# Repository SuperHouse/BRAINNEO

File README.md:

Building Brain Home Automation Controller (NanoPi NEO version)
===============================================================
Copyright 2017 SuperHouse Automation Pty Ltd  www.superhouse.tv  

Home automation controller based on a NanoPi NEO. The NEO
attaches to this board, which is Arduino-compatible (ATmega328P) and
includes 433MHz transmitter and receiver modules connected to the
Arduino. The Arduino can communicate with the NEO via serial, and
can send / receive RF messages using the 433MHz modules.

Features:

 * ATmega328P MCU
 * 433MHz transmitter
 * 433MHz receiver
 * Status LEDs

INSTALLATION
------------
The design is saved as an EAGLE project. EAGLE PCB design software is
available from www.cadsoftusa.com free for non-commercial use. To use
this project download it and place the directory containing these files
into the "eagle" directory on your computer. Then open EAGLE and
navigate to the project.

CREDITS
-------
Designed by Jonathan Oxer jon@oxer.com.au

DISTRIBUTION
------------
The specific terms of distribution of this project are governed by the
license referenced below.

LICENSE
-------
Licensed under the TAPR Open Hardware License (www.tapr.org/OHL).
The "license" folder within this repository also contains a copy of
this license in plain text format.

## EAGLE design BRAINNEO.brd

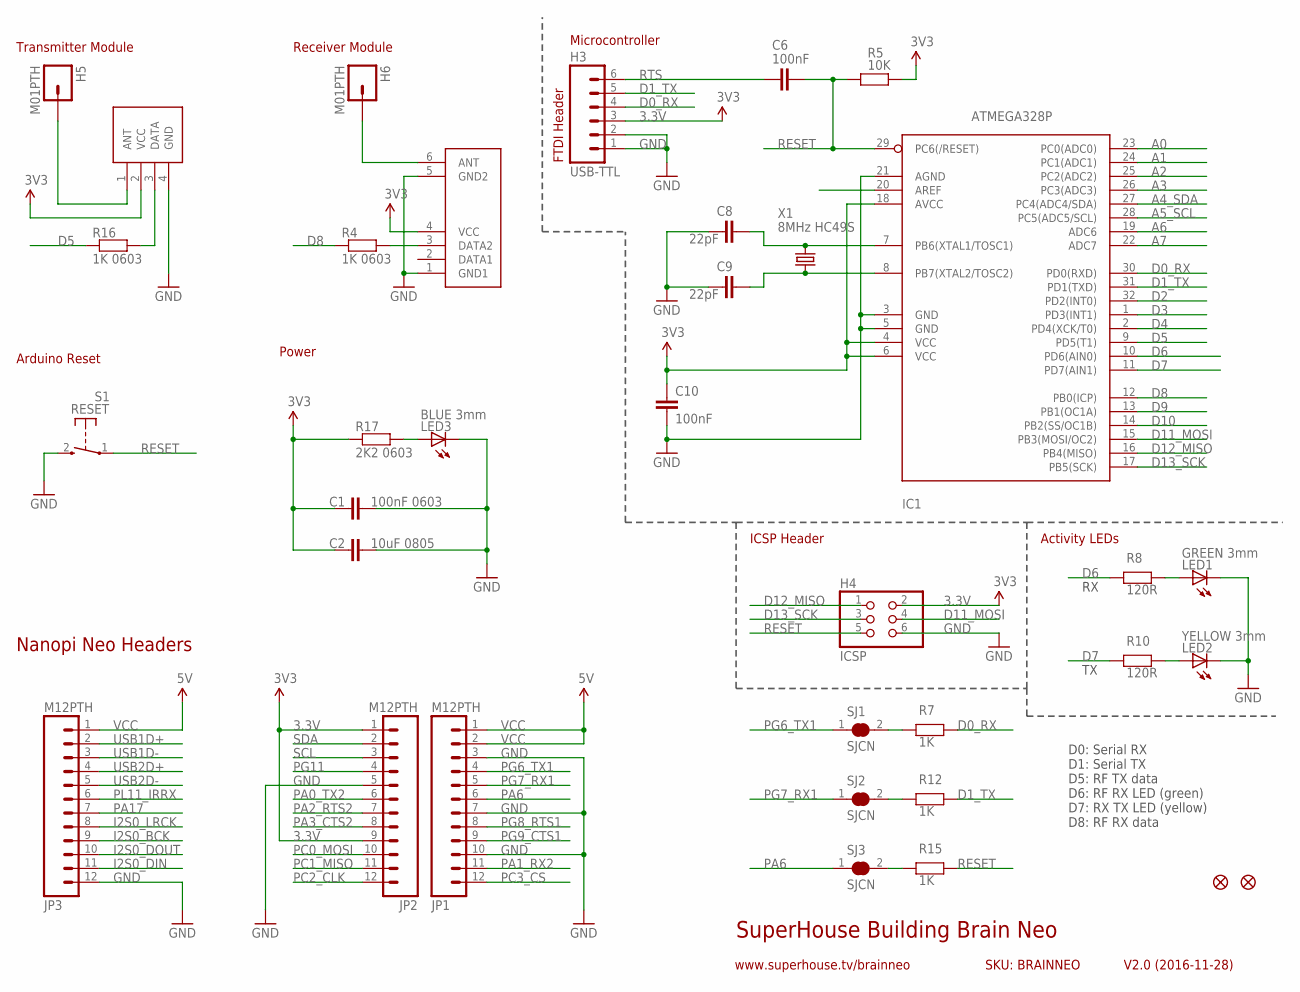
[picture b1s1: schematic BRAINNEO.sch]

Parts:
C1: 100nF 0603; 0603
C2: 10uF 0805; C0805
C6, C10: 100nF; 0603
C8, C9: 22pF; 0603
H3: USB-TTL; 1X06
H4: ICSP; 2X03
H5, H6: M01PTH; 1X01
IC1: ATMEGA328P; TQFP32-08
IC3: RXB1; RX-B1-SHORT-FLAT
IC4: TX-C1FLAT; TX-C1-FLAT
JP1, JP2, JP3: M12PTH; 1X12
LED1: GREEN 3mm; LED3MM
LED2: YELLOW 3mm; LED3MM
LED3: BLUE 3mm; LED3MM
R4, R16: 1K 0603; 0603
R5: 10K; 0603
R7, R12, R15: 1K; 0603
R8, R10: 120R; 0603
R17: 2K2 0603; 0603
S1: RESET; TACTILE_SWITCH_SMD_2PIN_TINY
SJ1, SJ2, SJ3: SJCN; SJC
U$5, U$6: FIDUCIAL1X2.5; FIDUCIAL-1X2.5
X1: 8MHz HC49S; HC49U-V

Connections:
3.3V: C1.1, C2.2, C10.1, H3.3, H4.2, IC1.4 (VCC), IC1.6 (VCC), IC1.18 (AVCC), IC3.4 (VCC), IC4.2 (VCC), JP2.1, JP2.9, R5.2, R17.1
A0: IC1.23 (PC0(ADC0))
A1: IC1.24 (PC1(ADC1))
A2: IC1.25 (PC2(ADC2))
A3: IC1.26 (PC3(ADC3))
A4_SDA: IC1.27 (PC4(ADC4/SDA))
A5_SCL: IC1.28 (PC5(ADC5/SCL))
A6: IC1.19 (ADC6)
A7: IC1.22 (ADC7)
AREF: IC1.20 (AREF)
D0_RX: H3.4, IC1.30 (PD0(RXD)), R7.1
D1_TX: H3.5, IC1.31 (PD1(TXD)), R12.1
D2: IC1.32 (PD2(INT0))
D3: IC1.1 (PD3(INT1))
D4: IC1.2 (PD4(XCK/T0))
D5: IC1.9 (PD5(T1)), R16.1
D6: IC1.10 (PD6(AIN0)), R8.2
D7: IC1.11 (PD7(AIN1)), R10.2
D8: IC1.12 (PB0(ICP)), R4.1
D9: IC1.13 (PB1(OC1A))
D10: IC1.14 (PB2(SS/OC1B))
D11_MOSI: H4.4, IC1.15 (PB3(MOSI/OC2))
D12_MISO: H4.1, IC1.16 (PB4(MISO))
D13_SCK: H4.3, IC1.17 (PB5(SCK))
GND: C1.2, C2.1, C8.1, C9.1, C10.2, H3.1, H3.2, H4.6, IC1.3 (GND), IC1.5 (GND), IC1.21 (AGND), IC3.1 (GND1), IC3.5 (GND2), IC4.4 (GND), JP1.3, JP1.7, JP1.10, JP2.5, JP3.12, LED1.K (C), LED2.K (C), LED3.K (C), S1.2 (S)
I2S0_BCK: JP3.9
I2S0_DIN: JP3.11
I2S0_DOUT: JP3.10
I2S0_LRCK: JP3.8
unnamed: IC3.3 (DATA2), R4.2
unnamed: LED3.A, R17.2
unnamed: H6.1, IC3.6 (ANT)
unnamed: H5.1, IC4.1 (ANT)
unnamed: IC4.3 (DATA), R16.2
unnamed: C8.2, IC1.7 (PB6(XTAL1/TOSC1)), X1.2
unnamed: C9.2, IC1.8 (PB7(XTAL2/TOSC2)), X1.1
unnamed: LED1.A, R8.1
unnamed: LED2.A, R10.1
unnamed: R7.2, SJ1.2
unnamed: R12.2, SJ2.2
unnamed: R15.2, SJ3.2
PA0_TX2: JP2.6
PA1_RX2: JP1.11
PA2_RTS2: JP2.7
PA3_CTS2: JP2.8
PA6: JP1.6, SJ3.1
PA17: JP3.7
PC0_MOSI: JP2.10
PC1_MISO: JP2.11
PC2_CLK: JP2.12
PC3_CS: JP1.12
PG6_TX1: JP1.4, SJ1.1
PG7_RX1: JP1.5, SJ2.1
PG8_RTS1: JP1.8
PG9_CTS1: JP1.9
PG11: JP2.4
PL11_IRRX: JP3.6
RESET: C6.2, H4.5, IC1.29 (PC6(/RESET)), R5.1, R15.1, S1.1
RTS: C6.1, H3.6
SCL: JP2.3
SDA: JP2.2
USB1D+: JP3.2
USB1D-: JP3.3
USB2D+: JP3.4
USB2D-: JP3.5
VCC: JP1.1, JP1.2, JP3.1

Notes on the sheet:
Nanopi Neo Headers
Power
Receiver Module
D0: Serial RX D1: Serial TX D5: RF TX data D6: RF RX LED (green) D7: RX TX LED (yellow) D8: RF RX data
ICSP Header
Microcontroller
FTDI Header
Transmitter Module
Arduino Reset
Activity LEDs
SuperHouse Building Brain Neo
V2.0 (2016-11-28)
www.superhouse.tv/brainneo
SKU: BRAINNEO

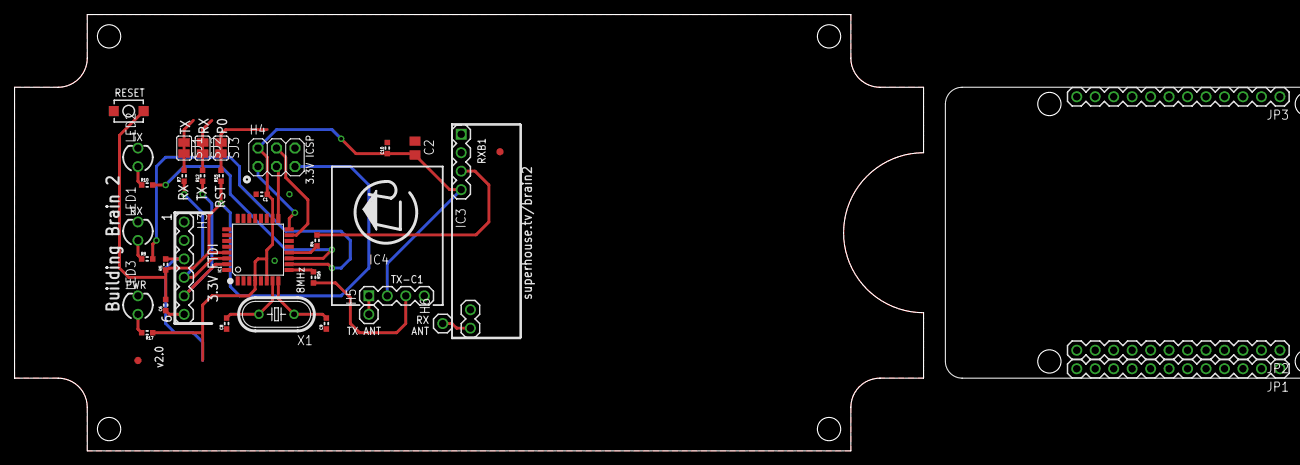
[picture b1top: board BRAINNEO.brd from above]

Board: 2 copper layers, 125.0 x 60.0 mm, 35 parts (0 on the bottom side), 29 nets.

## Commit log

2018-03-27 Initial import of rough project

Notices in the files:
BRAINNEO.brd:
(c) 2016 SuperHouse Automation
